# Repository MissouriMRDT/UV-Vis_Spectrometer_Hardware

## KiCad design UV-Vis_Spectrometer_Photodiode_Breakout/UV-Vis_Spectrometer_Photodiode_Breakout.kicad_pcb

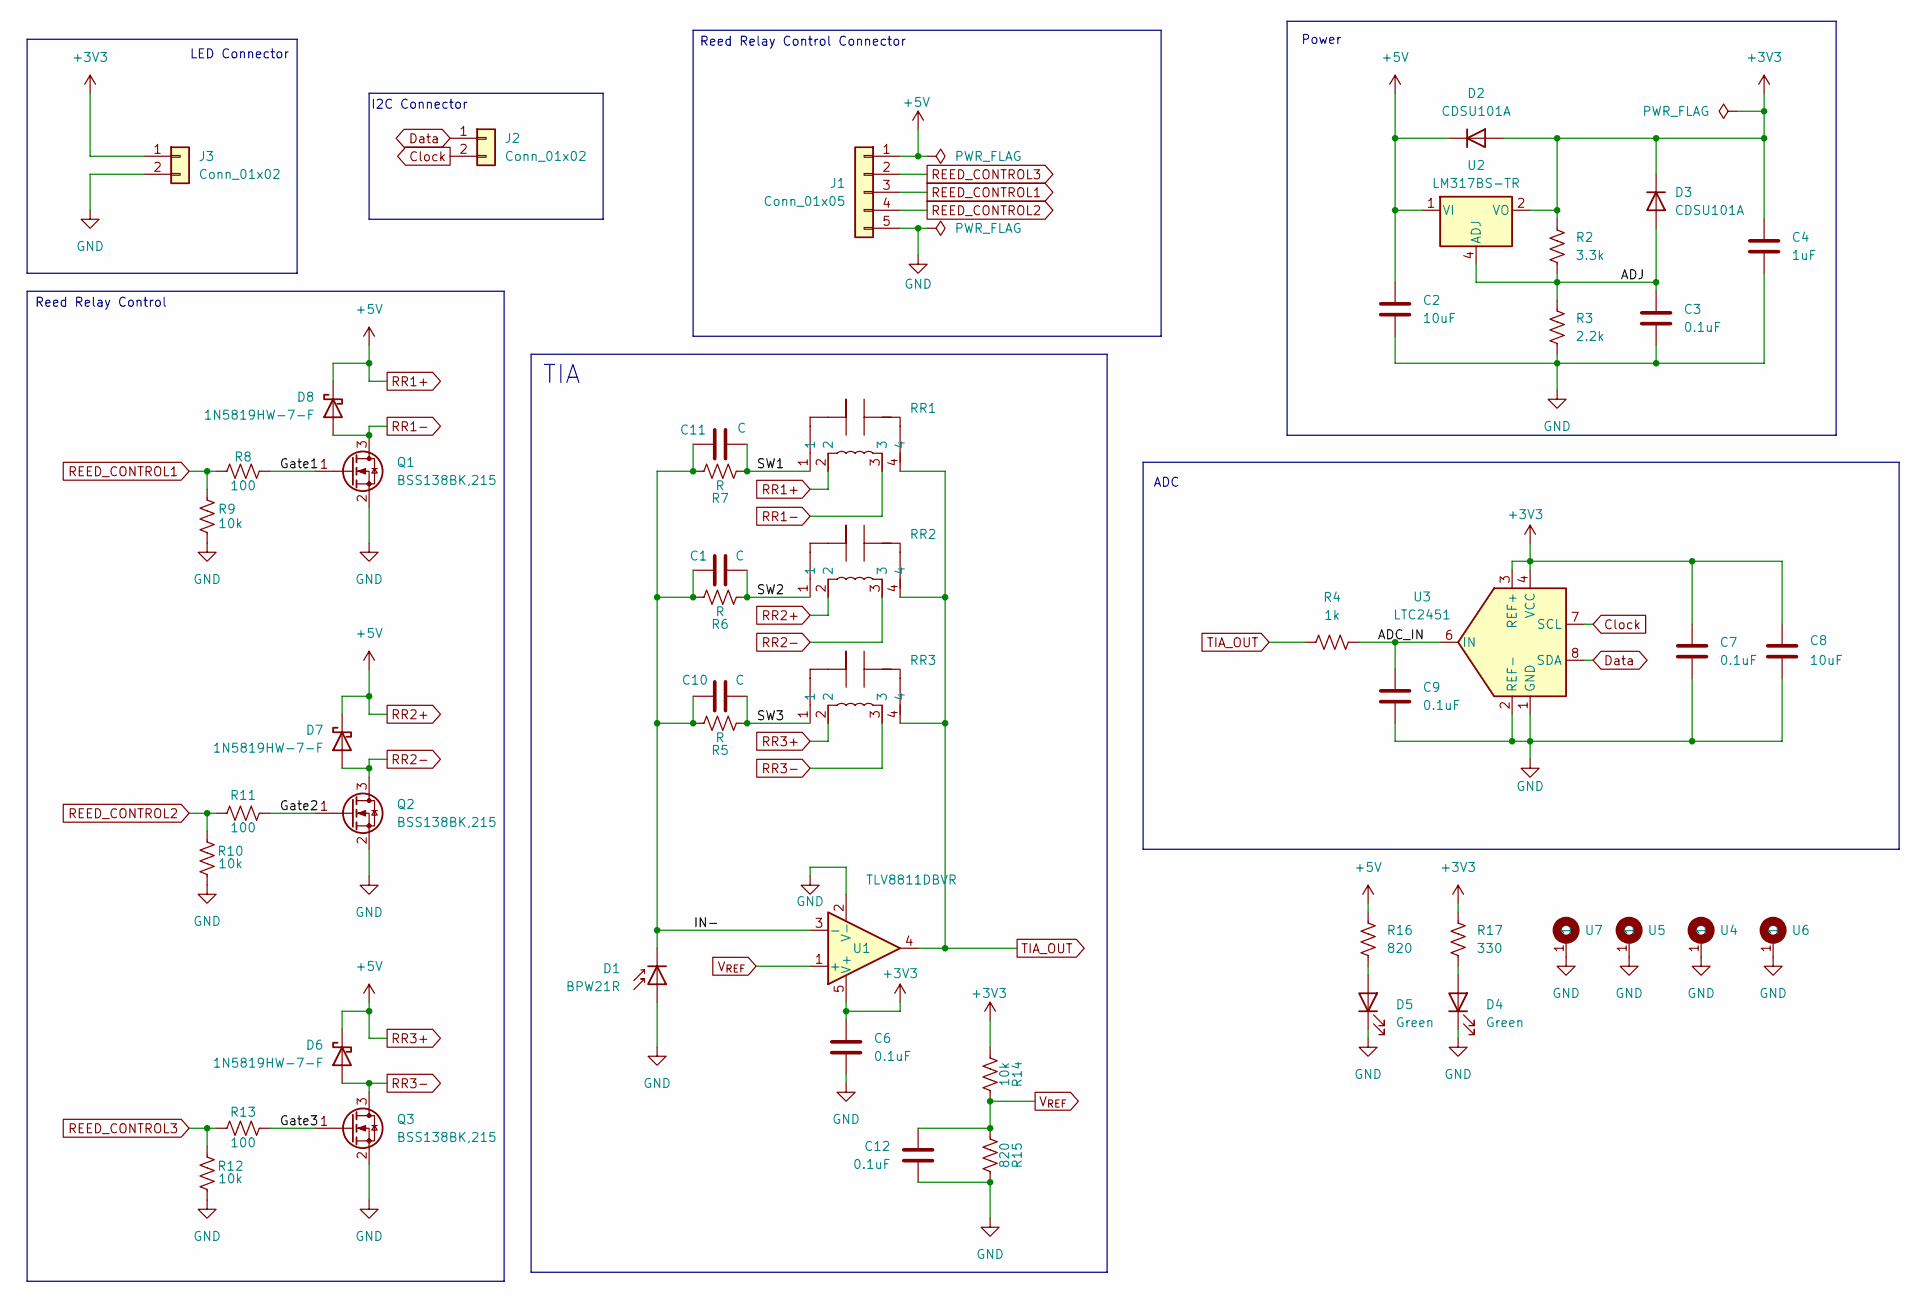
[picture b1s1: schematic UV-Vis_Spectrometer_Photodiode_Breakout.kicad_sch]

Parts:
C1, C10, C11: C; C_0603_1608Metric_Pad1.08x0.95mm_HandSolder
C2, C8: 10uF; C_0603_1608Metric_Pad1.08x0.95mm_HandSolder
C3, C6, C7, C9, C12: 0.1uF; C_0603_1608Metric_Pad1.08x0.95mm_HandSolder
C4: 1uF; C_0603_1608Metric_Pad1.08x0.95mm_HandSolder
D1: BPW21R
D2, D3: CDSU101A; D_0603_1608Metric_Pad1.05x0.95mm_HandSolder
D4, D5: Green; LED_0603_1608Metric_Pad1.05x0.95mm_HandSolder
D6, D7, D8: 1N5819HW-7-F; D_SOD-123
J1: Conn_01x05; JST_PH_S5B-PH-K_1x05_P2.00mm_Horizontal
J2, J3: Conn_01x02; JST_PH_S2B-PH-K_1x02_P2.00mm_Horizontal
Q1, Q2, Q3: BSS138BK,215; SOT-23
R2: 3.3k; R_0603_1608Metric_Pad0.98x0.95mm_HandSolder
R3: 2.2k; R_0603_1608Metric_Pad0.98x0.95mm_HandSolder
R4: 1k; R_0603_1608Metric_Pad0.98x0.95mm_HandSolder
R5, R6, R7: R; R_0603_1608Metric_Pad0.98x0.95mm_HandSolder
R8, R11, R13: 100; R_0603_1608Metric_Pad0.98x0.95mm_HandSolder
R9, R10, R12, R14: 10k; R_0603_1608Metric_Pad0.98x0.95mm_HandSolder
R15, R16: 820; R_0603_1608Metric_Pad0.98x0.95mm_HandSolder
R17: 330; R_0603_1608Metric_Pad0.98x0.95mm_HandSolder
RR1, RR2, RR3: Relay_SPDT_9007_05_00
U1: TLV8811DBVR; SOT-23-5_HandSoldering
U2: LM317BS-TR; SOIC-8_3.9x4.9mm_P1.27mm
U3: LTC2451; TSOT-23-8
U4, U5, U6, U7: 4_40_Hole_Pad_Via

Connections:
+3V3: C4.1, C6.2, C7.1, C8.1, D2.2 (A), D3.1 (K), J3.1, R2.1, R14.2, R17.1, U1.5 (V+), U2.2 (VO), U2.3 (VO), U2.6 (VO), U2.7 (VO), U3.3 (REF+), U3.4 (VCC)
/ADC_IN: C9.1, R4.2, U3.6 (IN)
/ADJ: C3.1, D3.2 (A), R2.2, R3.1, U2.4 (ADJ)
/Gate1: Q1.1 (G), R8.2
/Gate2: Q2.1 (G), R11.2
/Gate3: Q3.1 (G), R13.2
/IN-: C1.1, C10.1, C11.1, D1.1 (K), R5.1, R6.1, R7.1, U1.3 (-)
/SW1: C11.2, R7.2, RR1.1
/SW2: C1.2, R6.2, RR2.1
/SW3: C10.2, R5.2, RR3.1
Clock: J2.2, U3.7 (SCL)
Data: J2.1, U3.8 (SDA)
GND: C2.2, C3.2, C4.2, C6.1, C7.2, C8.2, C9.2, C12.2, D1.2 (A), D4.1 (K), D5.1 (K), J1.5, J3.2, Q1.2 (S), Q2.2 (S), Q3.2 (S), R3.2, R9.1, R10.1, R12.1, R15.1, U1.2 (V-), U3.1 (GND), U3.2 (REF-), U3.5 (GND), U4.1 (1_1), U5.1 (1_1), U6.1 (1_1), U7.1 (1_1)
unnamed: D4.2 (A), R17.2
unnamed: D5.2 (A), R16.2
REED_CONTROL1: J1.3, R8.1, R9.2
REED_CONTROL2: J1.4, R10.2, R11.1
REED_CONTROL3: J1.2, R12.2, R13.1
RR1+: C2.1, D2.1 (K), D6.1 (K), D7.1 (K), D8.1 (K), J1.1, R16.1, RR1.2, RR2.2, RR3.2, U2.1 (VI)
RR1-: D8.2 (A), Q1.3 (D), RR1.3
RR2-: D7.2 (A), Q2.3 (D), RR2.3
RR3-: D6.2 (A), Q3.3 (D), RR3.3
TIA_OUT: R4.1, RR1.4, RR2.4, RR3.4, U1.4
V_{REF}: C12.1, R14.1, R15.2, U1.1 (+)

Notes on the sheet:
I2C Connector
Reed Relay Control
ADC
Reed Relay Control Connector
LED Connector
Power
TIA

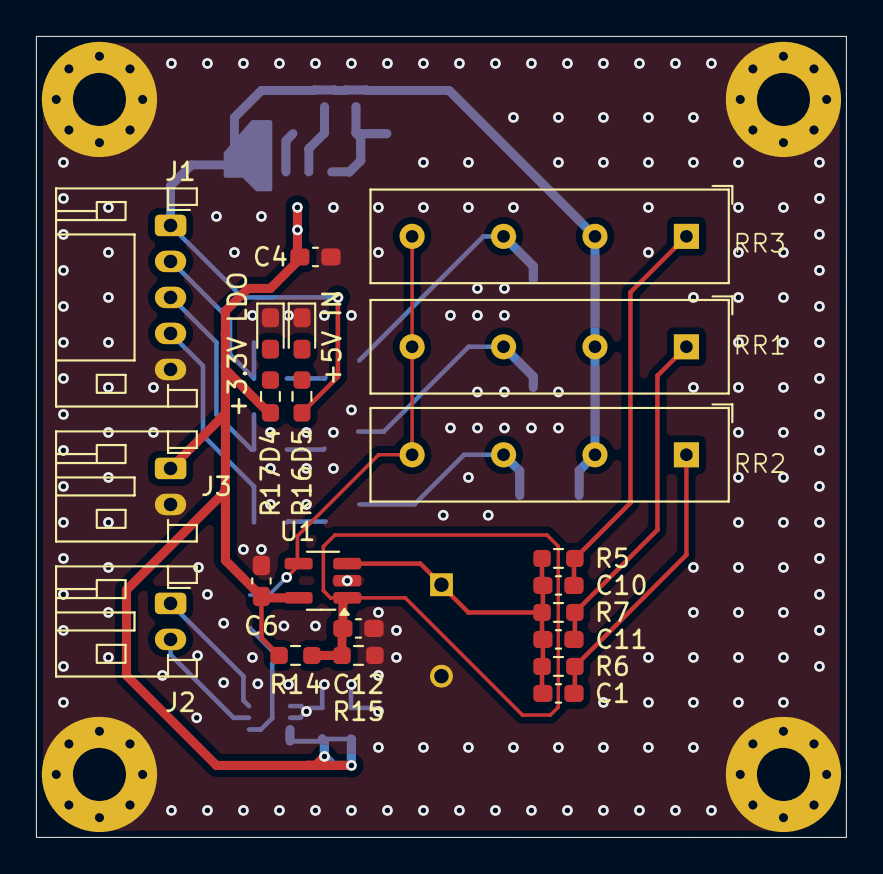
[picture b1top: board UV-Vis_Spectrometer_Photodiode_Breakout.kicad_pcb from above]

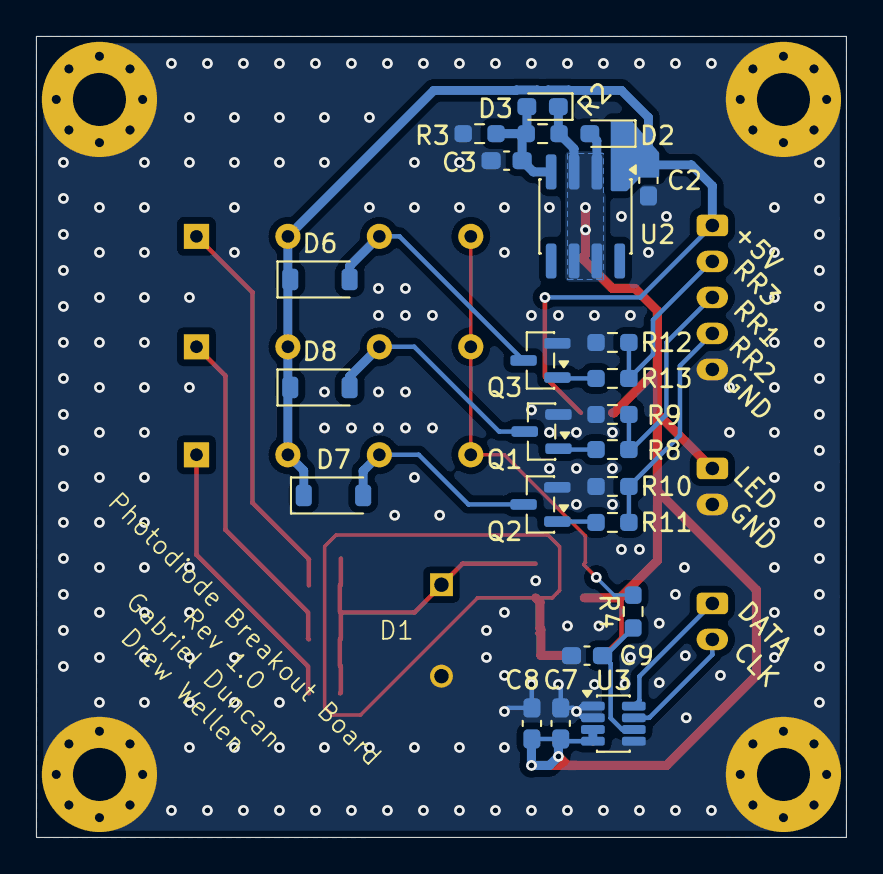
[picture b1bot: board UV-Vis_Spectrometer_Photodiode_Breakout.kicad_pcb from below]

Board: 2 copper layers, 45.0 x 44.5 mm, 51 parts (25 on the bottom side), 24 nets.

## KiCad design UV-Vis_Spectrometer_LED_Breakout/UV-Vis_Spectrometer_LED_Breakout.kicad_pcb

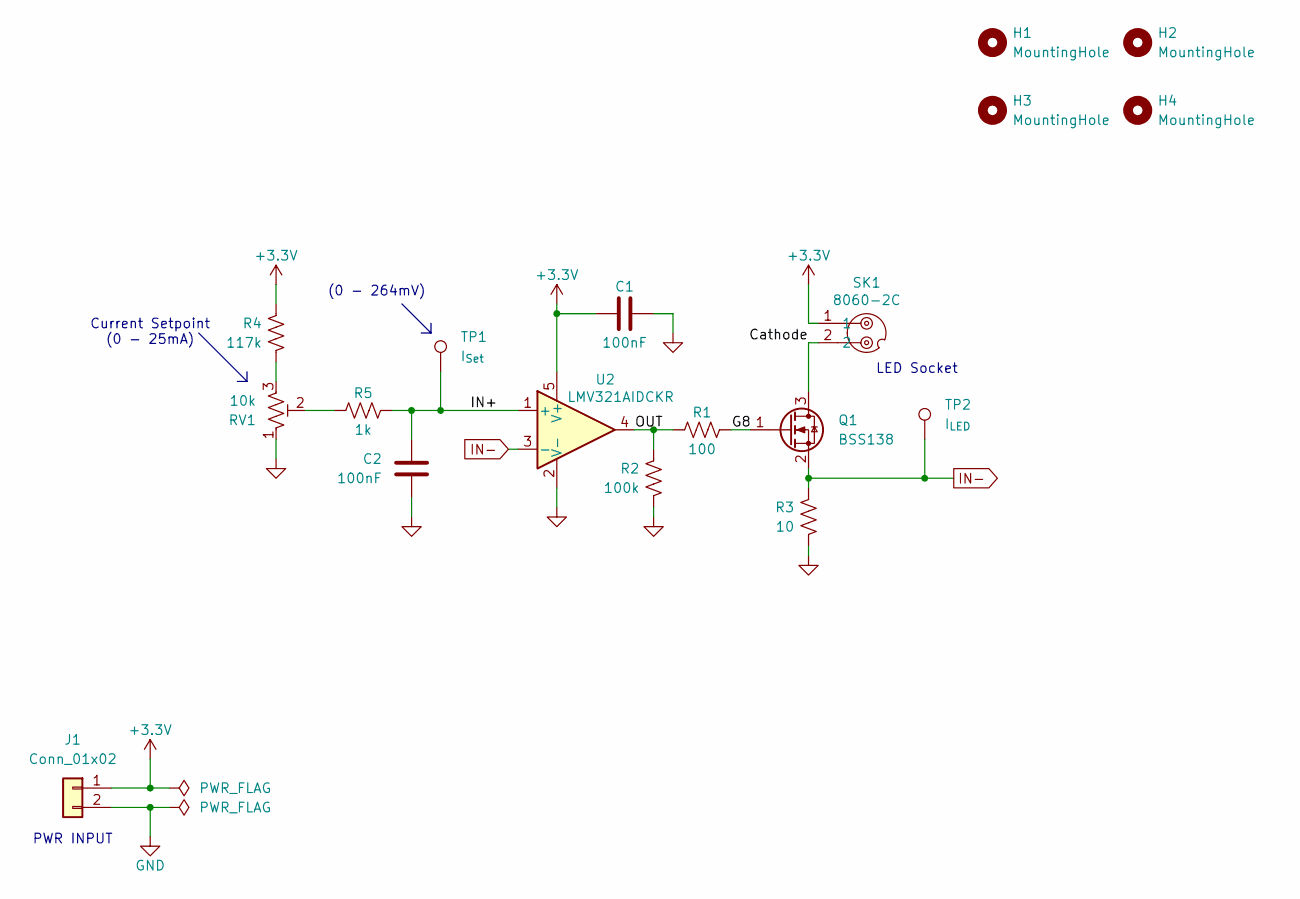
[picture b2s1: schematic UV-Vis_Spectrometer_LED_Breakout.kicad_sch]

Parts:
C1, C2: 100nF; C_0603_1608Metric
H1, H2, H3, H4: MountingHole; 4_40_Hole_Pad_Via
J1: Conn_01x02; JST_EH_B2B-EH-A_1x02_P2.50mm_Vertical
Q1: BSS138; SOT-23
R1: 100; R_0603_1608Metric
R2: 100k; R_0603_1608Metric
R3: 10; R_0603_1608Metric
R4: 117k; R_0603_1608Metric
R5: 1k; R_0603_1608Metric
RV1: 10k; Potentiometer_Bourns_3296W_Vertical
SK1: 8060-2C
TP1: I_{Set}; TestPoint_Pad_D1.5mm
TP2: I_{LED}; TestPoint_Pad_D1.5mm
U2: LMV321AIDCKR; SOT-353_SC-70-5

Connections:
+3.3V: C1.1, J1.1, R4.2, SK1.1, U2.5 (V+)
CS/FB: Q1.2 (S), R3.2, TP2.1 (1_1), U2.3 (-)
GND: C1.2, C2.2, J1.2, R2.1, R3.1, RV1.1, U2.2 (V-)
unnamed: Q1.3 (D), SK1.2
unnamed: Q1.1 (G), R1.2
unnamed: R1.1, R2.2, U2.4
unnamed: R4.1, RV1.3
unnamed: R5.1, RV1.2
unnamed: C2.1, R5.2, TP1.1 (1_1), U2.1 (+)

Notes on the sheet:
Current Setpoint (0 - 25mA)
PWR INPUT
LED Socket
(0 - 264mV)

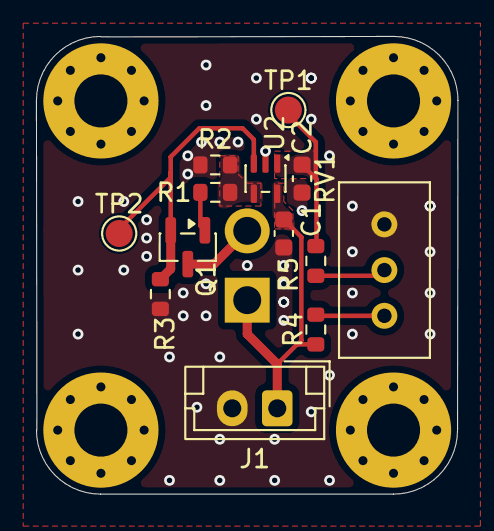
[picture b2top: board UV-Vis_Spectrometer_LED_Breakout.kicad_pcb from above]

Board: 2 copper layers, 23.4 x 25.4 mm, 18 parts (1 on the bottom side), 9 nets.
